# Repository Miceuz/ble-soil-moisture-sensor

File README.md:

# ble-soil-moisture-sensor
Bluetooth Low Energy - based soil moisture sensor

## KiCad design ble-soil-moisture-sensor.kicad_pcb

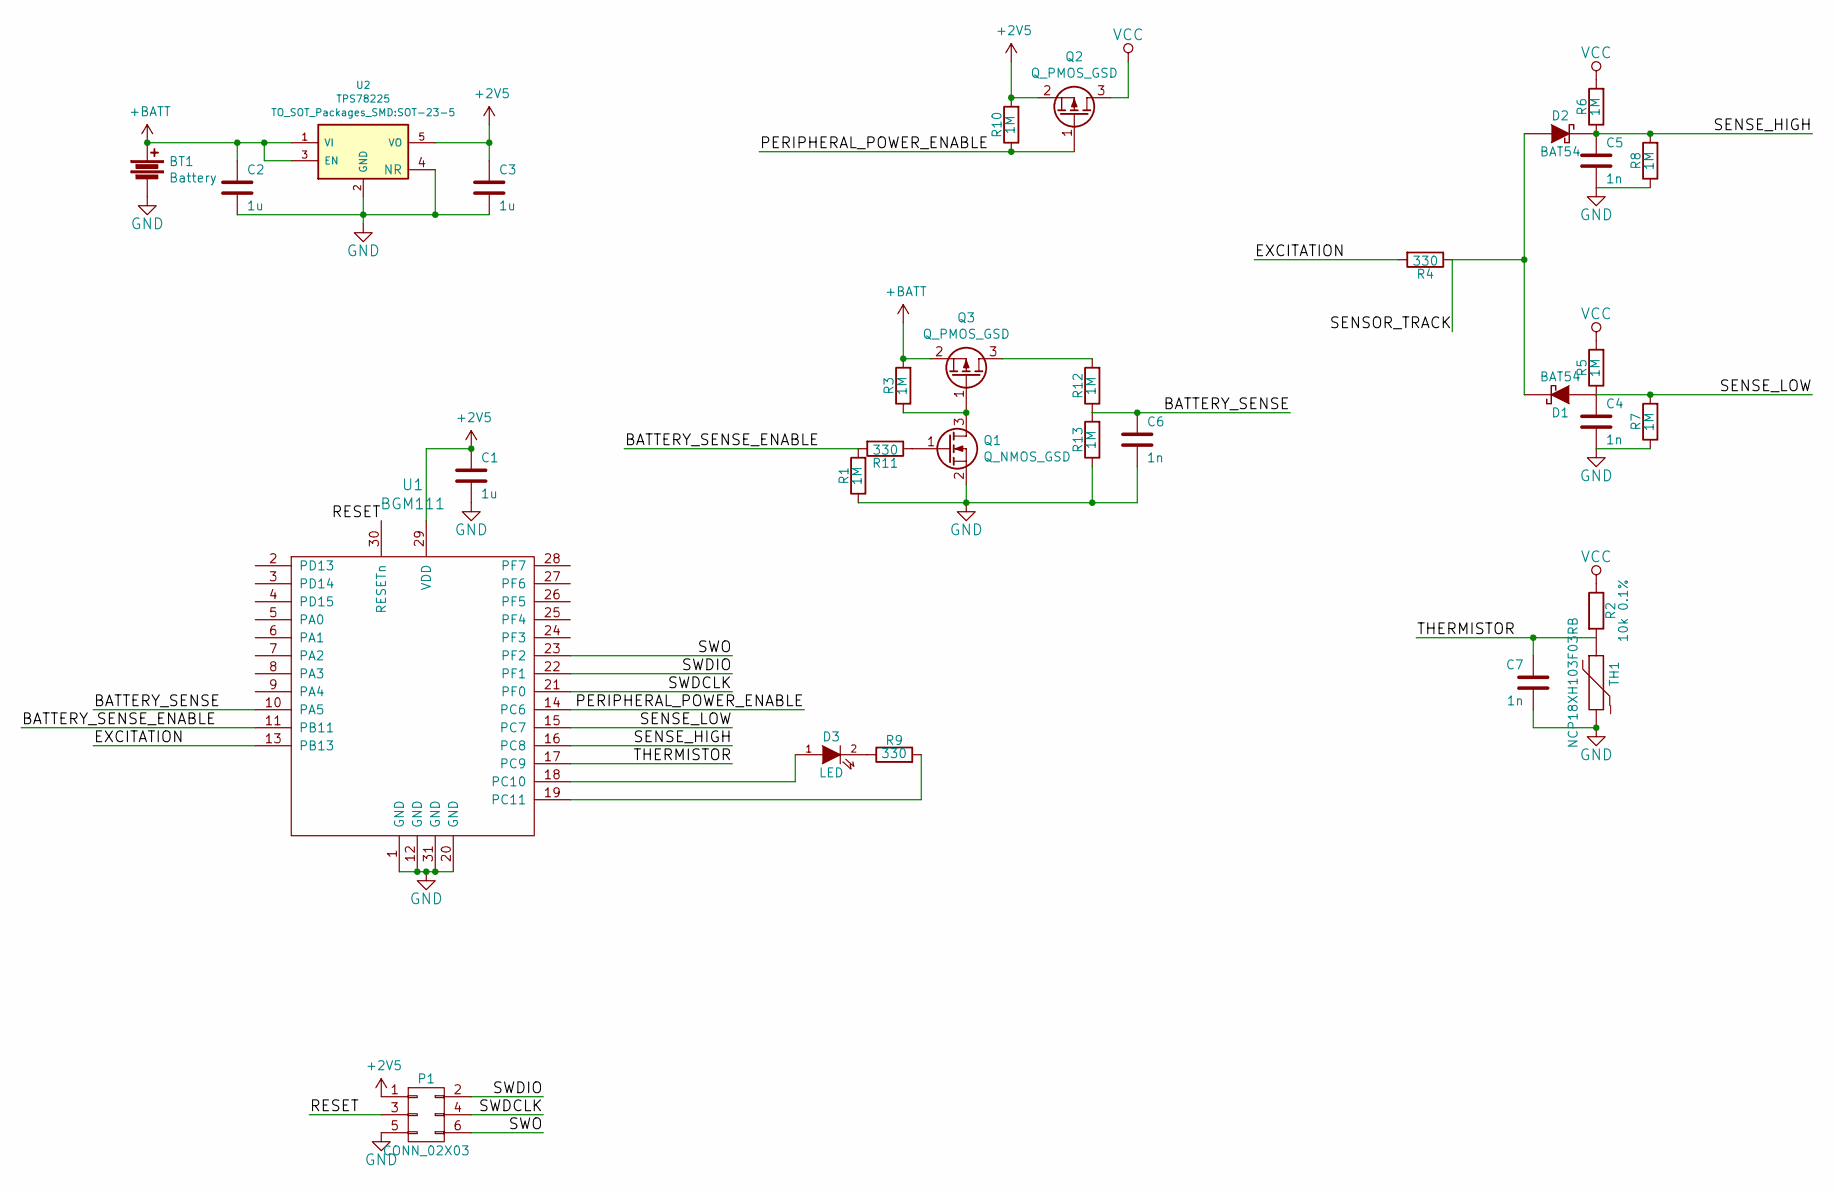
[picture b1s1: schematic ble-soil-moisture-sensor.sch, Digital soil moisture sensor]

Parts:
BT1: Battery; BAT-HLD-001; PartNo ?
C1, C2, C3: 1u; C_0603; PartNo MC0603X105K100CT
C4, C5, C6, C7: 1n; C_0603; PartNo MC0603B102K500CT
D1, D2: BAT54; SOD-523; PartNo BAT54XV2
D3: LED; LED-0603; PartNo KP-1608SURCK
P1: CONN_02X03; Pin_Header_Straight_2x03
Q1: Q_NMOS_GSD; SOT-23_Handsoldering; PartNo ?
Q2, Q3: Q_PMOS_GSD; SOT-23_Handsoldering; PartNo ?
R1, R3, R5, R6, R7, R8, R10, R12, R13: 1M; R_0603; PartNo MCWR06X1004FTL
R2: 10k 0.1%; R_0603; PartNo ERJ3RBD1002V
R4, R9, R11: 330; R_0603; PartNo MCWR06X3300FTL
TH1: NCP18XH103F03RB; R_0603; PartNo NCP18XH103F03RB
U1: BGM111; PartNo ?
U2: TPS78225; SOT-23-5; PartNo TPS78225DDCT

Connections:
+2V5: C1.1, C3.1, P1.1, Q2.2 (S), R10.2, U1.29 (VDD), U2.5 (VO)
+BATT: BT1.1, C2.1, Q3.2 (S), R3.2, U2.1 (VI), U2.3 (EN)
/BATTERY_SENSE: C6.1, R12.1, R13.2, U1.10 (PA5)
/BATTERY_SENSE_ENABLE: R1.2, R11.2, U1.11 (PB11)
/EXCITATION: R4.2, U1.13 (PB13)
/PERIPHERAL_POWER_ENABLE: Q2.1 (G), R10.1, U1.14 (PC6)
/RESET: P1.3, U1.30 (RESETn)
/SENSE_HIGH: C5.1, D2.2 (K), R6.1, R8.2, U1.16 (PC8)
/SENSE_LOW: C4.1, D1.1 (A), R5.1, R7.2, U1.15 (PC7)
/SENSOR_TRACK: D1.2 (K), D2.1 (A), R4.1
/SWDCLK: P1.4, U1.21 (PF0)
/SWDIO: P1.2, U1.22 (PF1)
/SWO: P1.6, U1.23 (PF2)
/THERMISTOR: C7.1, R2.2, TH1.1, U1.17 (PC9)
GND: BT1.2, C1.2, C2.2, C3.2, C4.2, C5.2, C6.2, C7.2, P1.5, Q1.2 (S), R1.1, R7.1, R8.1, R13.1, TH1.2, U1.1 (GND), U1.12 (GND), U1.20 (GND), U1.31 (GND), U2.2 (GND), U2.4 (NR); also elsewhere on the board
unnamed: D3.1 (A), U1.18 (PC10)
unnamed: D3.2 (K), R9.1
unnamed: Q1.1 (G), R11.1
unnamed: Q1.3 (D), Q3.1 (G), R3.1
unnamed: Q3.3 (D), R12.2
unnamed: R9.2, U1.19 (PC11)
VCC: Q2.3 (D), R2.1, R5.2, R6.2

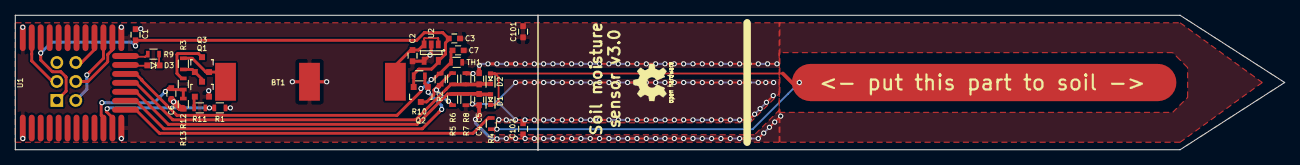
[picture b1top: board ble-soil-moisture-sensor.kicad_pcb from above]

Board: 2 copper layers, 170.0 x 18.0 mm, 33 parts (1 on the bottom side), 22 nets.

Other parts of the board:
C101, C102: C_0603

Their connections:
GND: C101.1, C101.2, C102.1, C102.2; also elsewhere on the board

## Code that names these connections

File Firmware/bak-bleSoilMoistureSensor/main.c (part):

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


#define BATTERY_SENSE_ENABLE BATTERY_SENSE_ENABLE_PORT, BATTERY_SENSE_ENABLE_PIN
#define PERIPHERAL_POWER_ENABLE PERIPHERAL_POWER_ENABLE_PORT, PERIPHERAL_POWER_ENABLE_PIN
#define EXCITATION EXCITATION_PORT, EXCITATION_PIN
#define LED_CATHODE LED_CATHODE_PORT, LED_CATHODE_PIN
#define LED_ANODE LED_ANODE_PORT, LED_ANODE_PIN

#define ADC_CHANNEL_BATTERY adcPosSelAPORT4XCH13      /*PA5*/
#define ADC_CHANNEL_MOISTURE_HIGH adcPosSelAPORT2XCH7 /*PC7*/
#define ADC_CHANNEL_MOISTURE_LOW adcPosSelAPORT1XCH8  /*PC8*/
#define ADC_CHANNEL_TEMPERATURE adcPosSelAPORT2XCH9   /*PC9*/

#define ADVERTISING_MOISTURE_ID 0x01
#define ADVERTISING_TEMPERATURE_ID 0x02
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volatile uint16 batteryVoltage = 0;

inline static void batterySenseOn() {
	GPIO_PinOutSet(BATTERY_SENSE_ENABLE);
}

inline static void batterySenseOff() {
	GPIO_PinOutClear(BATTERY_SENSE_ENABLE);
}

void lightSleepForTicks(uint32 ticks) {
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}

inline static void sensingPowerOn() {
	GPIO_PinOutClear(PERIPHERAL_POWER_ENABLE);
}

inline static void sensingPowerOff() {
	GPIO_PinOutSet(PERIPHERAL_POWER_ENABLE);
}

inline static void capSensExcitationStart() {
	GPIO_PinModeSet(EXCITATION, gpioModePushPull, 0);
	TIMER_TopSet(TIMER0, 0);
	TIMER_CompareSet(TIMER0, 0, 0);
	TIMER_Enable(TIMER0, true);
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
inline static void capSensExcitationStop() {
	TIMER_Enable(TIMER0, false);
	GPIO_PinOutClear(EXCITATION);
	GPIO_PinModeSet(EXCITATION, gpioModeDisabled, 0);
}

uint32 measureMoisture() {
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
	GPIO_PinModeSet(gpioPortC, 10, gpioModePushPull, 0);

	/* Pin PC11 is configured to Push-pull */
	GPIO_PinModeSet(gpioPortC, 11, gpioModePushPull, 0);

	GPIO_PinOutClear(LED_CATHODE);
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
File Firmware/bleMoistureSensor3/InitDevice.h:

//=========================================================
// inc/InitDevice.h: generated by Hardware Configurator
//
// This file will be regenerated when saving a document.
// leave the sections inside the "$[...]" comment tags alone
// or they will be overwritten!
//=========================================================
#ifndef __INIT_DEVICE_H__
#define __INIT_DEVICE_H__

// USER CONSTANTS
// USER PROTOTYPES

// $[Mode Transition Prototypes]
extern void enter_DefaultMode_from_RESET(void);
// [Mode Transition Prototypes]$

// $[Config(Per-Module Mode)Transition Prototypes]
extern void EMU_enter_DefaultMode_from_RESET(void);
extern void LFXO_enter_DefaultMode_from_RESET(void);
extern void CMU_enter_DefaultMode_from_RESET(void);
extern void ADC0_enter_DefaultMode_from_RESET(void);
extern void ACMP0_enter_DefaultMode_from_RESET(void);
extern void ACMP1_enter_DefaultMode_from_RESET(void);
extern void IDAC0_enter_DefaultMode_from_RESET(void);
extern void RTCC_enter_DefaultMode_from_RESET(void);
extern void USART0_enter_DefaultMode_from_RESET(void);
extern void USART1_enter_DefaultMode_from_RESET(void);
extern void LEUART0_enter_DefaultMode_from_RESET(void);
extern void WDOG0_enter_DefaultMode_from_RESET(void);
extern void I2C0_enter_DefaultMode_from_RESET(void);
extern void GPCRC_enter_DefaultMode_from_RESET(void);
extern void LDMA_enter_DefaultMode_from_RESET(void);
extern void TIMER0_enter_DefaultMode_from_RESET(void);
extern void TIMER1_enter_DefaultMode_from_RESET(void);
extern void LETIMER0_enter_DefaultMode_from_RESET(void);
extern void CRYOTIMER_enter_DefaultMode_from_RESET(void);
extern void PCNT0_enter_DefaultMode_from_RESET(void);
extern void PRS_enter_DefaultMode_from_RESET(void);
extern void PORTIO_enter_DefaultMode_from_RESET(void);
// [Config(Per-Module Mode)Transition Prototypes]$

// $[User-defined pin name abstraction]

#define BATTERY_SENSE_ENABLE_PIN            (11)
#define BATTERY_SENSE_ENABLE_PORT           (gpioPortB)

#define BATTERY_SENSE_PIN                   (5)
#define BATTERY_SENSE_PORT                  (gpioPortA)

#define EXCITATION_PIN                      (13)
#define EXCITATION_PORT                     (gpioPortB)

#define LED_ANODE_PIN                       (10)
#define LED_ANODE_PORT                      (gpioPortC)

#define LED_CATHODE_PIN                     (11)
#define LED_CATHODE_PORT                    (gpioPortC)

#define PERIPHERAL_POWER_ENABLE_PIN         (6)
#define PERIPHERAL_POWER_ENABLE_PORT        (gpioPortC)

#define SENSE_HIGH_PIN                      (7)
#define SENSE_HIGH_PORT                     (gpioPortC)

#define SENSE_LOW_PIN                       (8)
#define SENSE_LOW_PORT                      (gpioPortC)

#define THERMISTOR_PIN                      (9)
#define THERMISTOR_PORT                     (gpioPortC)

// [User-defined pin name abstraction]$

#endif

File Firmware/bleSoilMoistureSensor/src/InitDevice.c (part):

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
	// $[Port B Configuration]

	/* Pin PB11 is configured to Push-pull */
	GPIO_PinModeSet(gpioPortB, 11, gpioModePushPull, 0);

	/* Pin PB13 is configured to Push-pull */
	GPIO_PinModeSet(gpioPortB, 13, gpioModePushPull, 0);
	// [Port B Configuration]$

	// $[Port C Configuration]

	/* Pin PC6 is configured to Push-pull */
	GPIO_PinModeSet(gpioPortC, 6, gpioModePushPull, 0);

	/* Pin PC10 is configured to Push-pull */
	GPIO_PinModeSet(gpioPortC, 10, gpioModePushPull, 0);

	/* Pin PC11 is configured to Push-pull */
	GPIO_PinModeSet(gpioPortC, 11, gpioModePushPull, 0);
	// [Port C Configuration]$

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
	// $[Port F Configuration]

	/* Pin PF2 is configured to Push-pull */
	GPIO_PinModeSet(gpioPortF, 2, gpioModePushPull, 0);
	// [Port F Configuration]$

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
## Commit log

2016-11-11 Initial
2017-12-25 Add some fogotten schematics and pcb changes. Add BOM and firmware
2018-03-28 Update the firmware to new SDK, make it updateable over OTA

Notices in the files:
Firmware/bleSoilMoistureSensor/src/InitDevice.c:
Set up CC0
$[TIMER0 CC0 init]
$[TIMER1 CC0 init]
